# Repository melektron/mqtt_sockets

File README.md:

# Disclaimer

This is a PlatformIO "port" of an old of an old ESP8266 Arduino project that I did several years ago.
This code is by no means clean or memory safe and there are no guarantees of it working as expected. The only reason this old project is published in this state is so I can preserve it and fix bugs that arise over time as I need this in daily production. It has been working mostly reliably but use it at your own risk. 

Note to myself:
The folder "old_code" contains all the old code and versions that came about before I used git to store the project. These are just here for historical purposes and are not to be used. 

# MQTT Sockets

This project allows an ESP8266 connected to an MQTT server through WiFi and take commands from a SmartHome system like HomeAssistant. It then parses these commands and switches 433 MHz Remote controlled sockets on or off using a 433 MHz transmitter connected to the ESP. Multiple Remote-Socket protocols are supported.

## Project structure

This is a PIO project, so it has all the usual code folders. Additionally, the ```hardware``` folder contains KiCAD projects (legacy KiCAD project structure as these are old files):
- ```hardware/WiFi-RC-Switch-Bridge_Outlet```: The main PCB containing the ESP, RF-Transceivers and an integrated AC power supply for powering the board from the wall. This is what was used in the end.
- ```hardware/WiFi-RC-Switch-Bridge_USB```: At one point there was a plan to create a version of the board powered by USB. This contains the KiCAD project for that, although it was never completed.
- ```hardware/WiFi-RC-Switch-Programmer```: A USB-to-UART adapter based on CH340G to flash the ESP on the board. This has a connector matching the pinout of the header on the main PCB. Over the years, this has been used for many other projects and purposes.

## Setup

To use the project, you need to specify WIFI secrets, fingerprints and other configuration in the ```include/secrets.h``` file. Example content:

```c
#pragma once

#define WIFI_SSID "MyHomeWifi"
#define WIFI_PSK "MyWiFiPassword"

#define MQTT_SERVER "192.168.1.13"
#define MQTT_PORT 1883
// generate the fingerprint on the server using this command:
// echo | openssl s_client -connect localhost:1883 | openssl x509 -fingerprint -noout
#define MQTT_FINGERPRINT "07 ED 59 67 2C CD 31 6C EF 27 F7 AC 38 02 07 9C 60 EC FA 0A" // this isn't used at the moment because it didn't work
#define MQTT_BASE_TOPIC "/devices/sub0/espdev2051a/"
#define MQTT_USER "deviceuser"
#define MQTT_PWD  "devicepwd"

// when using DHCP do the following
#define WIFI_DHCP

// when using static IP do the following (replace with your correct IP settings)
// when WIFI_DHCP is defined, these values are ignored
#define WIFI_STATIC_IP 192,168,1,122
#define WIFI_STATIC_ROUTER 192,168,1,1
#define WIFI_STATIC_NETMASK 255,255,255,0

```

Of course, all the information has to be replaced by data applicable to your network setup.

Note to myself:
The values needed for my setup are found in the infrastructure setup notes.

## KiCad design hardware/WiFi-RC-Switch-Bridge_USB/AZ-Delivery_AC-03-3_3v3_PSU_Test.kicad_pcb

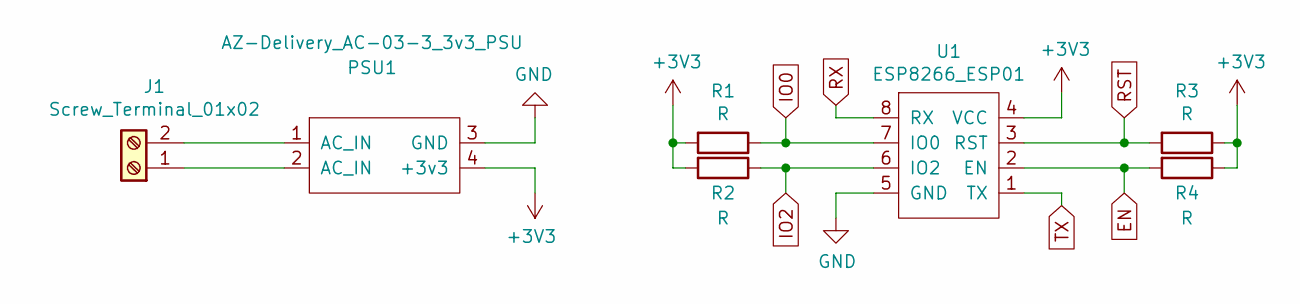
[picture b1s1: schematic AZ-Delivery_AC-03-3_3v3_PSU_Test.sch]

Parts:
J1: Screw_Terminal_01x02; TerminalBlock_bornier-2_P5.08mm
PSU1: AZ-Delivery_AC-03-3_3v3_PSU
R1, R2, R3, R4: R; R_Axial_DIN0207_L6.3mm_D2.5mm_P7.62mm_Horizontal
U1: ESP8266_ESP01

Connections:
+3V3: PSU1.4 (+3v3), R1.2, R2.2, R3.1, R4.1, U1.4 (VCC)
EN: R4.2, U1.2 (EN)
GND: PSU1.3 (GND), U1.5 (GND)
IO0: R1.1, U1.7 (IO0)
IO2: R2.1, U1.6 (IO2)
unnamed: J1.1, PSU1.2 (AC_IN)
unnamed: J1.2, PSU1.1 (AC_IN)
RST: R3.2, U1.3 (RST)
RX: U1.8 (RX)
TX: U1.1 (TX)

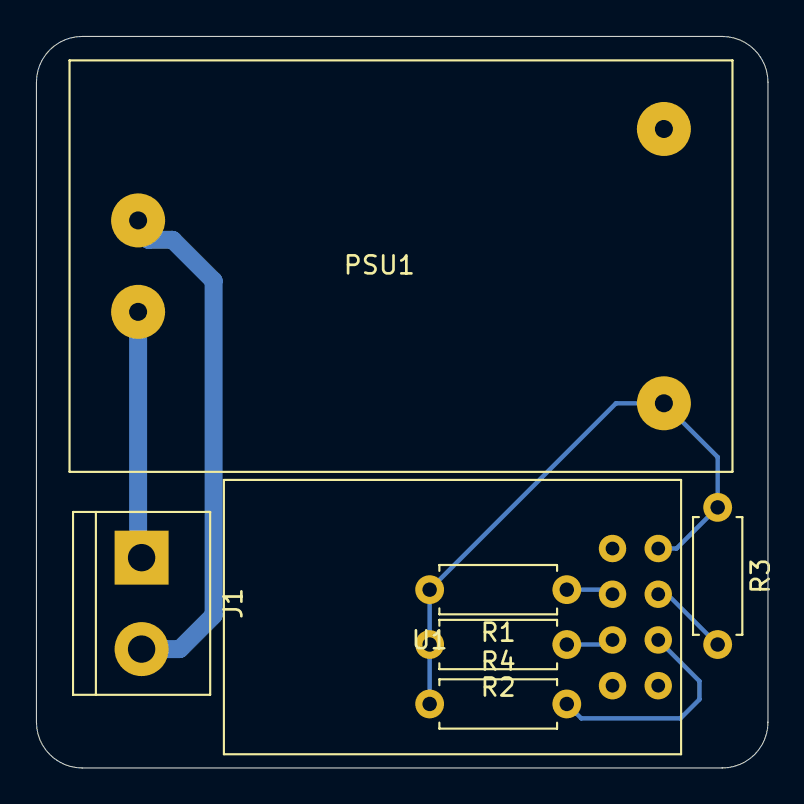
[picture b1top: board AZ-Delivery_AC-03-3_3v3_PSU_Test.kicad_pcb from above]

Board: 2 copper layers, 40.6 x 40.6 mm, 7 parts (0 on the bottom side), 8 nets.

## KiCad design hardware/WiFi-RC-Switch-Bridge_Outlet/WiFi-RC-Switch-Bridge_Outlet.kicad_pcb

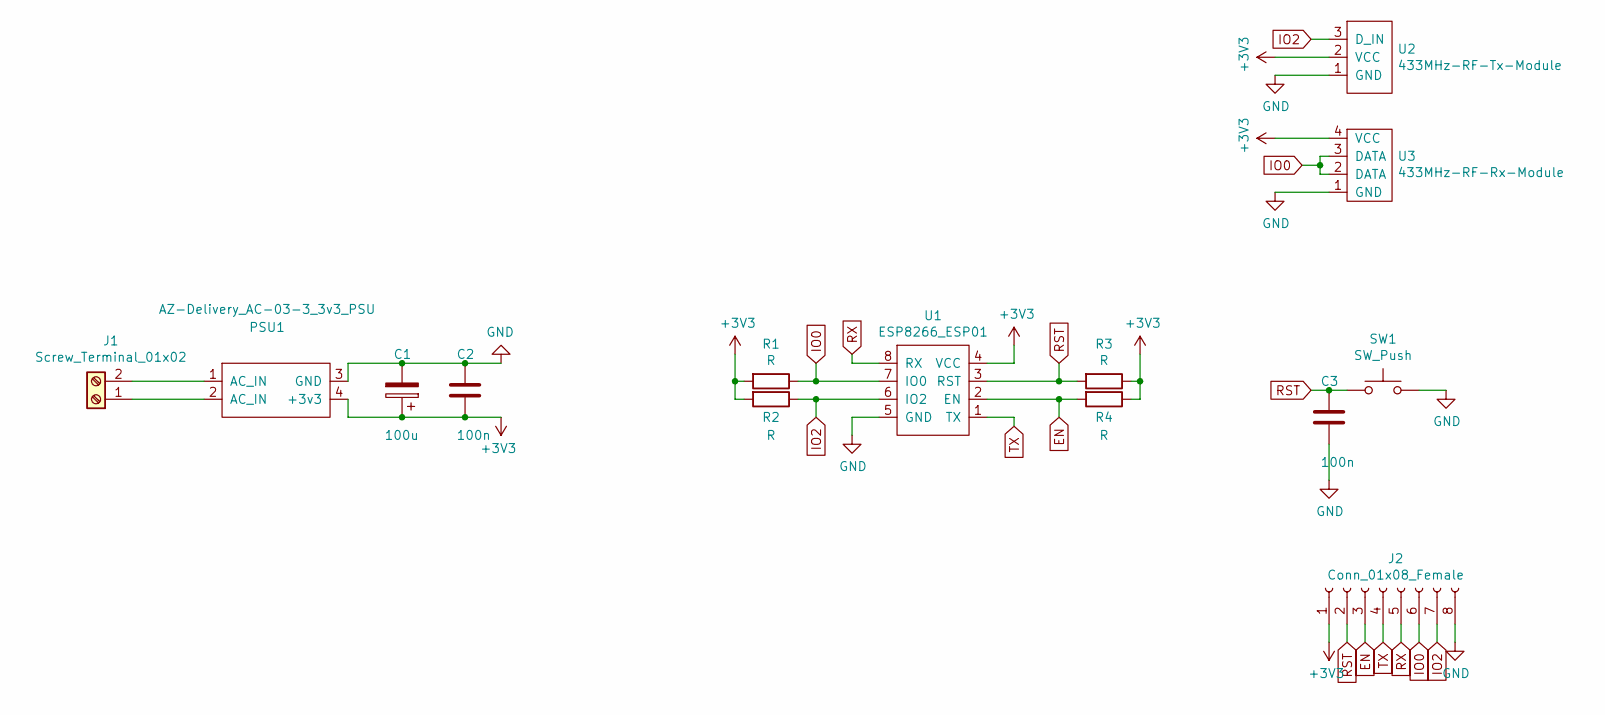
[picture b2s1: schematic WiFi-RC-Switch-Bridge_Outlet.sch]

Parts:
C1: 100u; CP_Radial_D5.0mm_P2.00mm
C2, C3: 100n; C_Disc_D6.0mm_W2.5mm_P5.00mm
J1: Screw_Terminal_01x02; TerminalBlock_bornier-2_P5.08mm
J2: Conn_01x08_Female; PinSocket_1x08_P2.54mm_Vertical
PSU1: AZ-Delivery_AC-03-3_3v3_PSU
R1, R2, R3, R4: R; R_Axial_DIN0207_L6.3mm_D2.5mm_P7.62mm_Horizontal
SW1: SW_Push; SW_PUSH_6mm_H5mm
U1: ESP8266_ESP01
U2: 433MHz-RF-Tx-Module; 433MHz-RF-Tx-Module_Horizontal
U3: 433MHz-RF-Rx-Module; 433MHz-RF-Rx-Module_Vertical

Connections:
+3V3: C1.1, C2.2, J2.1, PSU1.4 (+3v3), R1.2, R2.2, R3.1, R4.1, U1.4 (VCC), U2.2 (VCC), U3.4 (VCC)
EN: J2.3, R4.2, U1.2 (EN)
GND: C1.2, C2.1, C3.2, J2.8, PSU1.3 (GND), SW1.2, U1.5 (GND), U2.1 (GND), U3.1 (GND)
IO0: J2.6, R1.1, U1.7 (IO0), U3.2 (DATA), U3.3 (DATA)
IO2: J2.7, R2.1, U1.6 (IO2), U2.3 (D_IN)
unnamed: J1.1, PSU1.2 (AC_IN)
unnamed: J1.2, PSU1.1 (AC_IN)
RST: C3.1, J2.2, R3.2, SW1.1, U1.3 (RST)
RX: J2.5, U1.8 (RX)
TX: J2.4, U1.1 (TX)

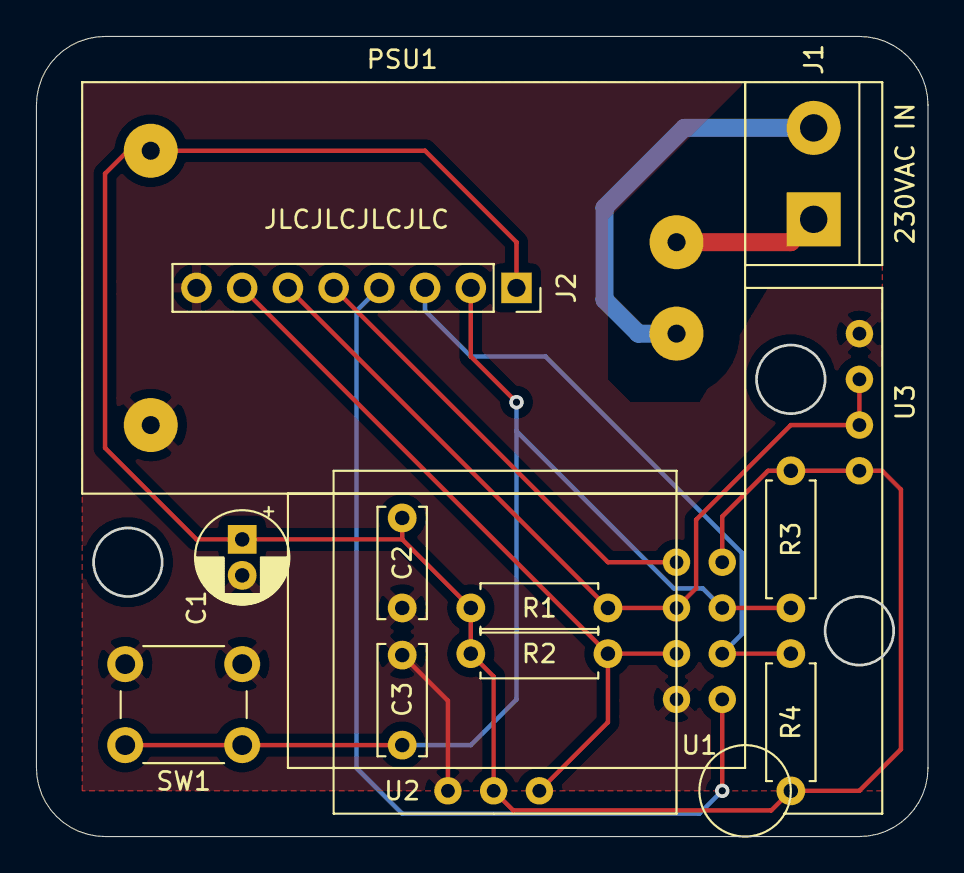
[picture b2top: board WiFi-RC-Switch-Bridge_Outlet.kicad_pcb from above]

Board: 2 copper layers, 49.4 x 44.4 mm, 14 parts (0 on the bottom side), 10 nets.

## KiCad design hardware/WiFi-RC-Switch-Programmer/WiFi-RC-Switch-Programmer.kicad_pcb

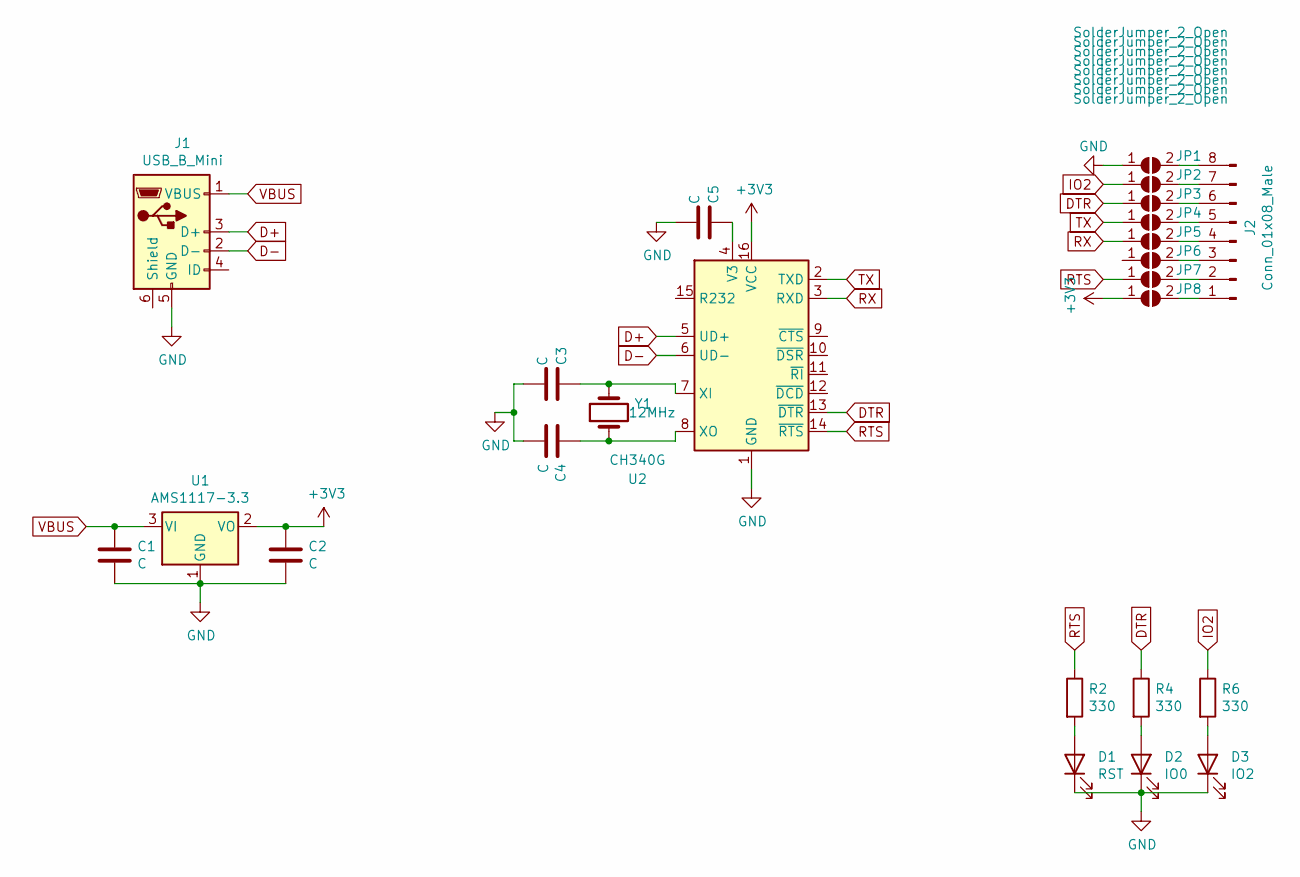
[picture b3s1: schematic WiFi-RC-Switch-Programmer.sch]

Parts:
C1, C2, C5: C; C_Disc_D6.0mm_W2.5mm_P5.00mm
C3, C4: C; C_Disc_D3.0mm_W2.0mm_P2.50mm
D1: RST; LED_D5.0mm
D2: IO0; LED_D5.0mm
D3: IO2; LED_D5.0mm
J1: USB_B_Mini; USB-MiniB_LCSC-C46398
J2: Conn_01x08_Male; PinHeader_1x08_P2.54mm_Horizontal
JP1, JP2, JP3, JP4, JP5, JP6, JP7, JP8: SolderJumper_2_Open; SolderJumper-2_P1.3mm_Open_RoundedPad1.0x1.5mm
R2, R4, R6: 330; R_0603_1608Metric_Pad0.98x0.95mm_HandSolder
U1: AMS1117-3.3; SOT-223-3_TabPin2
U2: CH340G; SOIC-16_3.9x9.9mm_P1.27mm
Y1: 12MHz; Crystal_HC49-4H_Vertical

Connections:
+3V3: C2.1, JP8.1 (A), U1.2 (VO), U2.16 (VCC)
D+: J1.3 (D+), U2.5 (UD+)
D-: J1.2 (D-), U2.6 (UD-)
DTR: JP3.1 (A), R4.1, U2.13 (~DTR)
GND: C1.2, C2.2, C3.2, C4.2, C5.2, D1.1 (K), D2.1 (K), D3.1 (K), J1.5 (GND), JP1.1 (A), U1.1 (GND), U2.1 (GND)
IO2: JP2.1 (A), R6.1
unnamed: C3.1, U2.7 (XI), Y1.2
unnamed: C4.1, U2.8 (XO), Y1.1
unnamed: C5.1, U2.4 (V3)
unnamed: D1.2 (A), R2.2
unnamed: D2.2 (A), R4.2
unnamed: D3.2 (A), R6.2
unnamed: J2.1, JP8.2 (B)
unnamed: J2.2, JP7.2 (B)
unnamed: J2.3, JP6.2 (B)
unnamed: J2.4, JP5.2 (B)
unnamed: J2.5, JP4.2 (B)
unnamed: J2.6, JP3.2 (B)
unnamed: J2.7, JP2.2 (B)
unnamed: J2.8, JP1.2 (B)
RTS: JP7.1 (A), R2.1, U2.14 (~RTS)
RX: JP5.1 (A), U2.3 (RXD)
TX: JP4.1 (A), U2.2 (TXD)
VBUS: C1.1, J1.1 (VBUS), U1.3 (VI)

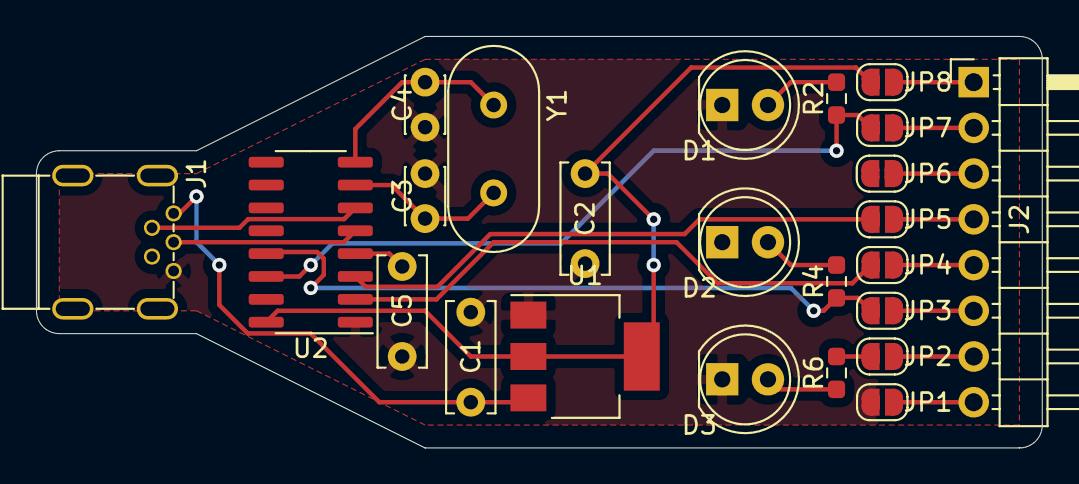
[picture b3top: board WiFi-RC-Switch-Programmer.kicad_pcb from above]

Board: 2 copper layers, 55.9 x 22.9 mm, 24 parts (0 on the bottom side), 24 nets.

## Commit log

2023-04-01 PIO Project init
2023-04-01 added README
2023-04-01 added old code, lib deps and README notes
2023-04-01 added more config options and got to work
2023-04-01 fixed integer comparison warnings
2023-04-01 added missing pragma once in readme example
2023-04-01 added mqtt server and port to secrets
2023-04-01 added all explicit version markings to deps
2025-02-22 retrospectively added old hardware design files

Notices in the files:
hardware/WiFi-RC-Switch-Bridge_Outlet/WiFi-RC-Switch-Bridge_Outlet.kicad_pcb:
© 2020 www.elektron.work
